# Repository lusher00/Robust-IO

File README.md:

# Robust IO

A rugged industrial I/O board designed in KiCad 10.

## Status

- **Rev A:** fabricated and assembled by JLCPCB (5 bare boards, 2 assembled),
  ordered 2026-10-05. Board 1 passes bring-up: power rails, MCU, UART
  console, MC33978 inputs (after replacing U7), MCP2515 CAN at 250 kbit/s
  with a BeagleBone Blue host, and all 8 outputs under TUI and CAN control
  (OUT_0's indicator LED is dead; the output itself works). Load test:
  OUT_0 to OUT_3 on together at about 3.7 A each, 14.8 A from 24 V, board
  cool on IR. Board 2 is partly disassembled from
  the reverse-polarity incident and needs C44/C45, U5, U1, U14 and one
  BTS7008 refitted.
- **Rev B:** change list collected below. The KiCad project in
  `hardware/rev-b/` starts as a copy of rev A.
- **Schematic:** complete across four hierarchical sheets. ERC clean.
- **PCB layout:** fully routed. DRC reports 0 errors and 4 library-mismatch
  warnings (J20, U1, U14, U7), which are intentional local footprint edits.

## Board

| Item | Value |
|---|---|
| Size | 160 x 100 mm, four M3 mounting holes |
| Layers | 4: F.Cu signal, In1 GND plane, In2 +24V plane, B.Cu signal |
| Copper | 2 oz outer, 1 oz inner |
| Minimum drill | 0.3 mm |
| Supply | 24 V nominal through a blade fuse (F1) and SMDJ24A TVS |
| Assembly | SMD parts on top side only; through-hole connectors and fuse holder hand-fitted |

## Architecture

| Sheet | Contents |
|---|---|
| `power` | Two TPS560430 buck regulators (+5V, +3.3V), input fuse, TVS, bulk capacitors |
| `processor` | ATmega1284P, MCP2515 + MCP2562 (CAN), crystals, ISP header (J1), UART header (J20), reset button |
| `inputs` | MC33978 22-channel switch detect with fused, filtered inputs and status LEDs |
| `outputs2` | Four BTS7008-2EPA dual high-side switches (8 outputs), two DRV8876 motor drivers |

## Connectors

- **J1:** 2x3 2.54 mm SMD header, AVR ISP (SPI is also on test points).
- **J20:** 1x6 2.54 mm SMD header, 3.3 V TTL UART in FTDI cable pinout.
  RX and TX have series resistors and a TVS array.
- **J14, J19, J18, J16, J9, J10 (top edge):** 3.5 mm pluggable terminal
  headers for the switch inputs, each with a fused supply pin and ground.
- **J15 (bottom edge):** 24 V supply input and ground.
- **J3, J5 (bottom edge):** high-side outputs OUT_0 to OUT_7, with +24V and
  ground.
- **J6 (bottom edge):** two motor driver outputs, with +24V and ground.
- **J4 (left edge):** CAN bus, +5V and ground. SW1 is next to it.

## Test points

41 test points (35 top, 6 bottom) cover the supply rails, SPI, UART, CAN
interrupt, driver control and sense lines, and ground. Positions and nets are
listed in `hardware/rev-a/fab/robust-io-testpoints.csv`.

## Known limits of rev A

- **Supply polarity is not marked on the board.** J15 pins 1 and 2 (the
  square pad end, nearest F1) are +24V; pins 3 and 4 are GND. There is no
  reverse-polarity protection, so a reversed supply forward-biases D6 and the
  substrate diodes of every part on the rail. Both rev A boards were powered
  reversed during bring-up; see the Bring-up log.
- **MC33978 input LEDs read "input at ground".** Each input LED sits between
  +24V (2.2k) and the IC pin, so it lights when the input is pulled low.
  That is correct for switch-to-ground sensing, which is all rev A
  supports; switch-to-battery on an SP channel needs that channel's LED
  removed, because the 2.2k sources more current than the IC can sink.
- **BTS7008 GND pins have no series resistor.** The datasheet calls for
  47 ohm in the GND pin (RGND) and limits GND pin current to 50 mA.
- **CS_CAN has no pull-up.** With the MCU in reset (during ISP) the MCP2515
  can drive MISO; programming is unreliable unless the board is power-cycled
  first. Fit 10k from TP8 to TP1 if it keeps failing.
- **UART activity LEDs load the lines.** C69/C70 (10 nF) with the 1k series
  resistors give a 10 us edge, too slow for 115200 baud. The console runs at
  38400 on rev A.
- **C57 to C60 use a polarized symbol** in the schematic; the fitted parts
  are 50 V MLCCs and have no polarity.

- The BTS7008-2EPA is rated for a 28 V maximum supply. Use a regulated 24 V
  supply; do not connect directly to a charging battery system.
- Reverse polarity protection is the fuse and TVS only. There is no series
  reverse-blocking stage.
- The input polyfuses are rated 30 V, which is a small margin over 24 V.
- Y1 load capacitors (22 pF) have not been matched to the crystal's
  specified load capacitance.
- Regulator output tracks are 0.2 mm wide.

## Bring-up log (rev A)

- Both boards were first powered with the supply reversed. The symptom was a
  rail that read like a diode (0.5 V both ways, about 2 Ohm at 1 A), with
  whichever part had the lowest forward drop getting warm: D6, then U5,
  then the BTS7008 switches and DRV8876 drivers as parts were removed. With
  the supply in current limit at about 1 V nothing was damaged except C44
  and C45 on board 2, which vented after conducting in reverse for a long
  time. D6 was correctly placed on both boards; the earlier CPL change for
  it has been reverted.
- Board 1 after correct power: 5 V and 3.3 V present, fuses written
  (JTAG off), firmware flashed from a Raspberry Pi over J1, console at
  38400 8N1 on J20, MCP2515 answers. MC33978 does not answer the SPI check:
  continuity from the MCU to U7 pins 2, 3, 4, 16, 31 and 32 is good, VBATP
  and VDDQ are present, all four SPI modes were tried. The MISO pull-up
  test in firmware 0.3 (`MC33978 check frames` line in the banner) is the
  next step: 0xFFFFFFFF means the chip never drives MISO, 0x00000000 means
  it is selected but not shifting.
- With JTAG enabled (fresh chip) outputs 2 to 5 switch on by themselves.
  They go off once the fuses are written.
- On a Pi 4, avrdude leaves GPIO25 (reset) driven low after it exits. Run
  `pinctrl set 25 ip pu` (or `raspi-gpio set 25 ip pu`) after programming,
  or unplug J1 pin 5, before expecting the board to run.
- The Pi's mini UART (`/dev/ttyS0`) is unreliable for the console even at
  38400. Use an FTDI cable on J20 for the console and the Pi only for
  programming, or switch the Pi to the PL011 (`dtoverlay=disable-bt`).

## Rev B change list

- MCU: replace the ATmega1284P + MCP2515 with an STM32G474 (Cortex-M4,
  170 MHz, 3 native FDCAN, 5 ADCs, HRTIM/advanced timers, native USB).
  Board CAN becomes CAN FD with an FD-rated transceiver. Programming over
  SWD (Tag-Connect or 10-pin header; Blue via OpenOCD, or the ESP32 over
  Wi-Fi). Freed pins mean the ESP32-S3 links to the MCU over a UART
  instead of joining the CAN bus (its TWAI is classic only and would break
  an FD bus), and USB-CAN runs on the G474's own USB. Firmware: drivers and
  CAN protocol port in C; the HAL layer is rewritten. An M7 (STM32H723)
  only if robust-io needs Ethernet itself.
- Mark + and - on the silkscreen at J15.
- 24 V input protection front end, in order from J15: F1 blade fuse, a
  surge stopper / ideal-diode controller rated for at least 100 V
  (LTC4368/LT4363 class) with back-to-back 100 V N-FETs, then the rail TVS
  after the FETs. The controller gives reverse polarity (to -40 V or
  better), overvoltage cutoff at about 30 V set by divider, undervoltage
  lockout, a forward/reverse overcurrent circuit breaker and soft-start for
  hot-plug inrush. Any TVS ahead of the FETs is bidirectional with a
  standoff above the worst wrong supply (SMDJ64CA class), so reverse
  polarity or a 48 to 60 V supply turns the board off instead of clamping
  and blowing F1. A rev A board was hit with 60 V on 2026-11-07: the
  SMDJ24A clamped, both 10 A fuses blew and the rail was left shorted.
  Move the bulk capacitors after the controller and rate them 100 V. Add a
  supply monitor (INA228-class: bus voltage, total current, fault alert) on
  the MCU so input V/I and protection trips are reported over CAN.
- Input indicator LEDs: two-lead bicolour LED (red/green) in series with each
  input, replacing the 2.2k pull-ups R62 to R83, so the LED shows current in
  either direction and switch-to-battery works on the SP channels. Checked
  against the MC33978 datasheet: detection threshold 4.0 V (3.7 to 4.3 V,
  80 to 300 mV hysteresis), sustain 2.0 mA SG / 2.2 mA SB. SG closed sits at
  the LED drop (about 2 V), at least 1.4 V under the minimum threshold; SB
  closed sits near +24V minus the drop. Use high-efficiency LEDs, visible at
  2 mA and rated for the 20 mA maximum wetting pulse. Do not use low-power
  mode (SG threshold 100 to 300 mV, below the LED drop) or the 2.5 V
  threshold option on these inputs. Put the LED after the input filter and
  clamp so field transients do not pass through it.
- 47 ohm in series with each BTS7008 GND pin (U8 to U11).
- C69/C70 to 220 pF, or drive the UART LEDs from the MCU.
- C57 to C60: non-polarized capacitor symbol.
- Test points: Keystone 5015 SMT loops on the rails, SPI, UART, interrupt,
  fault and analog sense lines; the four corner mounting holes are GND and
  take a ring lug, which covers the ground clips.
- SBC supply: 24 V to 5 V 5 A buck (Pi 5 / CM5) and 24 V to 12 V 3 A buck
  (BeagleBone Blue 9-18 V jack), each fused, on their own terminal block and
  fed from +24V ahead of the output switches so the host timeout cannot cut
  the host's own power.
- Use the bottom side: move the large SMC diodes (output clamps D2, D4,
  D8 to D13 B560C, D7 B340, input TVS D6) and other bulky parts to B.Cu for
  hand fitting, freeing top-side area around the output stage.
- Optional Wi-Fi/BLE: socket headers for a Waveshare ESP32-S3-Zero (same
  module as the POV project); the board works without it fitted. It joins
  the MCU over a UART (see MCU item), is wired to SWD and NRST/BOOT0 so it
  can reflash the MCU over Wi-Fi, and can bridge the console UART. Powered from +5V into the Zero's own regulator, so the +5V rail must
  cover its Wi-Fi peaks (about 350 to 500 mA).
  Bridge functions on the S3 (classic CAN only; CAN FD, Ethernet fieldbuses
  and Linux stay on the can-gateway):
  - Wi-Fi/BLE to CAN bridge: web UI, MQTT and a CAN socket for hosts.
  - USB-to-CAN adapter (candleLight/gs_usb class) on the G474's native USB
    via USB-C, so a Mac or PC gets a CAN FD interface.
  - One RS-485 port (Modbus RTU) from an S3 UART: transceiver, terminal
    block, switchable 120 ohm termination and bias.
- 16 high-side outputs, all on the protected 9 to 28 V input (12 V and
  24 V systems; vehicle load dump handled by the input front end):
  - OUT_0 to OUT_7: keep the four BTS7008-2EPA (7.5 A per channel).
  - OUT_8 to OUT_15: four 24 V-family duals (BTT6030-2ERA or TPS272C45,
    pick at schematic time), with margin above 28 V.
  - Each bank has its own output-power terminal, fed from the main input by
    default, so an E-stop or safety relay can cut output power while the MCU
    stays up and reporting. No separate 36 V injection.
  Size connector GND/supply pins per bank (rev A has one GND pin per four
  outputs on J3/J5).
- Replace the two DRV8876 (current limit fixed at about 1.36 A by
  resistors, too low for typical 2 to 5 A linear actuators) with two quad
  half-bridges (8 half-bridges), DRV8962 class (about 65 V, 5 A per half-bridge; confirm in
  the datasheet). Current limit set from a G474 DAC instead of fixed
  resistors, with per-half-bridge current sense to the ADC. Each
  half-bridge is configured in firmware as a high-side or low-side output,
  or paired for reversing: up to four reversing motors or linear actuators,
  four latching irrigation valve zones, two bipolar steppers, or any mix.
  Needs about 16 MCU control pins plus sense and fault lines (G474 in
  LQFP100).
- 4 relay outputs, dry contact (SPDT), for AC loads: 24 VAC irrigation
  valves, pump/fan contactor coils. Mains loads go through external
  contactors.
- Analog inputs: 4 channels, each jumper or software selectable 4-20 mA /
  0-10 V, protected, on G474 ADCs (tank level, pressure, soil moisture).
- 2 fast pulse inputs on G474 timer pins for flow meters and encoders.
- LoRa (SX1262 module) on the ESP32 side for remote sites beyond Wi-Fi.
- Connectors: replace Phoenix MSTBA/MC with LCSC-stocked equivalents of the
  same pitch (Degson/Kefa/Dinkle 5.08 mm for power, outputs and motors,
  3.5 mm for inputs; plugs about $0.30 to $1 instead of about $7), and
  standardize on as few pin counts as possible so one plug type covers
  each group. Prefer push-in spring plugs for the inputs.

## Repository layout

| Folder | Content |
|---|---|
| `hardware/rev-a/` | Rev A as built (git tag `rev-a`): KiCad project, `fab/` outputs and parts orders, `docs/` drawings and photos, `fixture/` bench fixture |
| `hardware/rev-b/` | Rev B KiCad project, in progress |
| `firmware/` | ATmega1284P firmware for rev A |
| `tools/` | Host tools, shared by both revisions (same CAN protocol) |
| `manufacturers datasheets/` | Part datasheets |

Rev A files stay as they were built; all new hardware work happens in
`hardware/rev-b/`.

### Rev A KiCad files (`hardware/rev-a/`)

- `robust-io.kicad_pro` - project file
- `robust-io.kicad_sch` - root sheet
- `power.kicad_sch`, `processor.kicad_sch`, `inputs.kicad_sch`, `outputs2.kicad_sch` - schematic sheets
- `robust-io.kicad_pcb` - PCB layout
- `robust-io.kicad_sym`, `sym-lib-table` - project symbol library
- `robust-io.kicad_dru` - custom design rules
- `DRC.rpt`, `ERC.rpt` - latest check reports

## Documentation (`hardware/rev-a/docs/`)

| File | Content |
|---|---|
| [robust-io-schematic.pdf](hardware/rev-a/docs/robust-io-schematic.pdf) | Schematic, all sheets |
| [layout-top.pdf](hardware/rev-a/docs/layout-top.pdf), [layout-bottom.pdf](hardware/rev-a/docs/layout-bottom.pdf) | Copper and silkscreen per side |
| [assembly-top.pdf](hardware/rev-a/docs/assembly-top.pdf) | Assembly drawing with reference designators |
| [board-top.png](hardware/rev-a/docs/board-top.png), [board-bottom.png](hardware/rev-a/docs/board-bottom.png), [board-angle.png](hardware/rev-a/docs/board-angle.png) | 3D renders |
| [robust-io-revA-top.jpg](hardware/rev-a/docs/robust-io-revA-top.jpg), [robust-io-revA-top-board-only.jpg](hardware/rev-a/docs/robust-io-revA-top-board-only.jpg) | Photos of the assembled rev A board (composite of several exposures, rectified to the board outline) |

Regenerate with `bash hardware/rev-a/docs/make_docs.sh` after saving the schematic and board.

## Firmware (`firmware/`)

ATmega1284P firmware 0.3: UART service console (38400 8N1), CAN protocol with
host timeout, output current trip, motor control, EEPROM settings and a
self-test. Runs on rev A hardware; the MC33978 driver is unverified until the
chip answers (see Bring-up log). Build with `make` in `firmware/` (avr-gcc); `make fuses` and
`make flash` program the board from a Raspberry Pi wired to J1. See
[firmware/DESIGN.md](firmware/DESIGN.md) for the pin map, console commands,
CAN frame layouts and settings.

## Host tools (`tools/`)

Everything for talking to the board over CAN from a Pi, laptop or robot:
a DBC file, a Python package with the `robustio` command-line tool, a terminal
dashboard, a browser dashboard, a bring-up and end-of-line test runner that
writes a report per board, a ROS 2 driver node, and `canweb`, a CAN
diagnostic web app for a Pi with a transceiver (live bus view, DBC decode,
send, log, and a Robust IO page with input lights, output buttons and current
graphs; other products plug in as a Python class). All of them also run
against the firmware simulator, so they can be used before hardware exists.
See [tools/README.md](tools/README.md).

## Fabrication outputs (`hardware/rev-a/fab/`)

| File | Purpose |
|---|---|
| `make_gerbers.sh` | Plots Gerbers, drill files and the position file with kicad-cli, then zips the Gerbers |
| `gerbers/`, `robust-io-gerbers.zip` | Gerber and Excellon drill files |
| `robust-io-BOM-JLC-smd.csv` | JLCPCB assembly BOM, 50 lines, LCSC part number on every line |
| `robust-io-CPL-JLC.csv` | JLCPCB placement file |
| `cpl_rotation_offsets.json` | Per-part rotation corrections applied to the placement file |
| `kicad-pos.csv` | Raw KiCad position export |
| `robust-io-BOM-tht.csv` | Through-hole parts to fit by hand (fuse holder, terminal headers) |
| `robust-io-testpoints.csv` | Test point list with nets and positions |
| `robust-io-fab-all.zip` | Everything above in one archive |

To regenerate the Gerbers after a board change, save the board in KiCad and run:

    bash hardware/rev-a/fab/make_gerbers.sh

The placement file is not produced by the script. JLCPCB's rotation
convention differs from KiCad's for some packages, so the rotation for each
part in `robust-io-CPL-JLC.csv` is the KiCad rotation plus the offset in
`cpl_rotation_offsets.json`. Regenerate it whenever parts move, and check
the result in JLCPCB's placement preview before ordering.

## Bring-up order

1. Fit F1 and J15. Apply 24 V from a current-limited supply with nothing else
   connected.
2. Check +5V (TP2) and +3.3V (TP1) against ground.
3. Wire the Raspberry Pi to J1 (`firmware/DESIGN.md` section 4) and run
   `make fuses`, then `make flash`, in `firmware/`. Do this before connecting
   any load to J3 or J5: until the fuses disable JTAG, outputs 2 to 5 can
   switch on by themselves. Release the reset line afterward
   (`pinctrl set 25 ip pu`).
4. On the J20 console (FTDI cable, 38400 8N1): `ver`, then `selftest`.
5. Connect CAN and run `robustio bringup --console /dev/serial0 --serial <n>`
   from `tools/`, which writes a report for the board.
6. Connect loads and enable the outputs and motor drivers one channel at a time
   (`robustio bringup --loads` once all are connected).

## License

See [LICENSE](LICENSE). Free for personal, educational, and open-source use.
For commercial licensing, contact ryan.lush@gmail.com.

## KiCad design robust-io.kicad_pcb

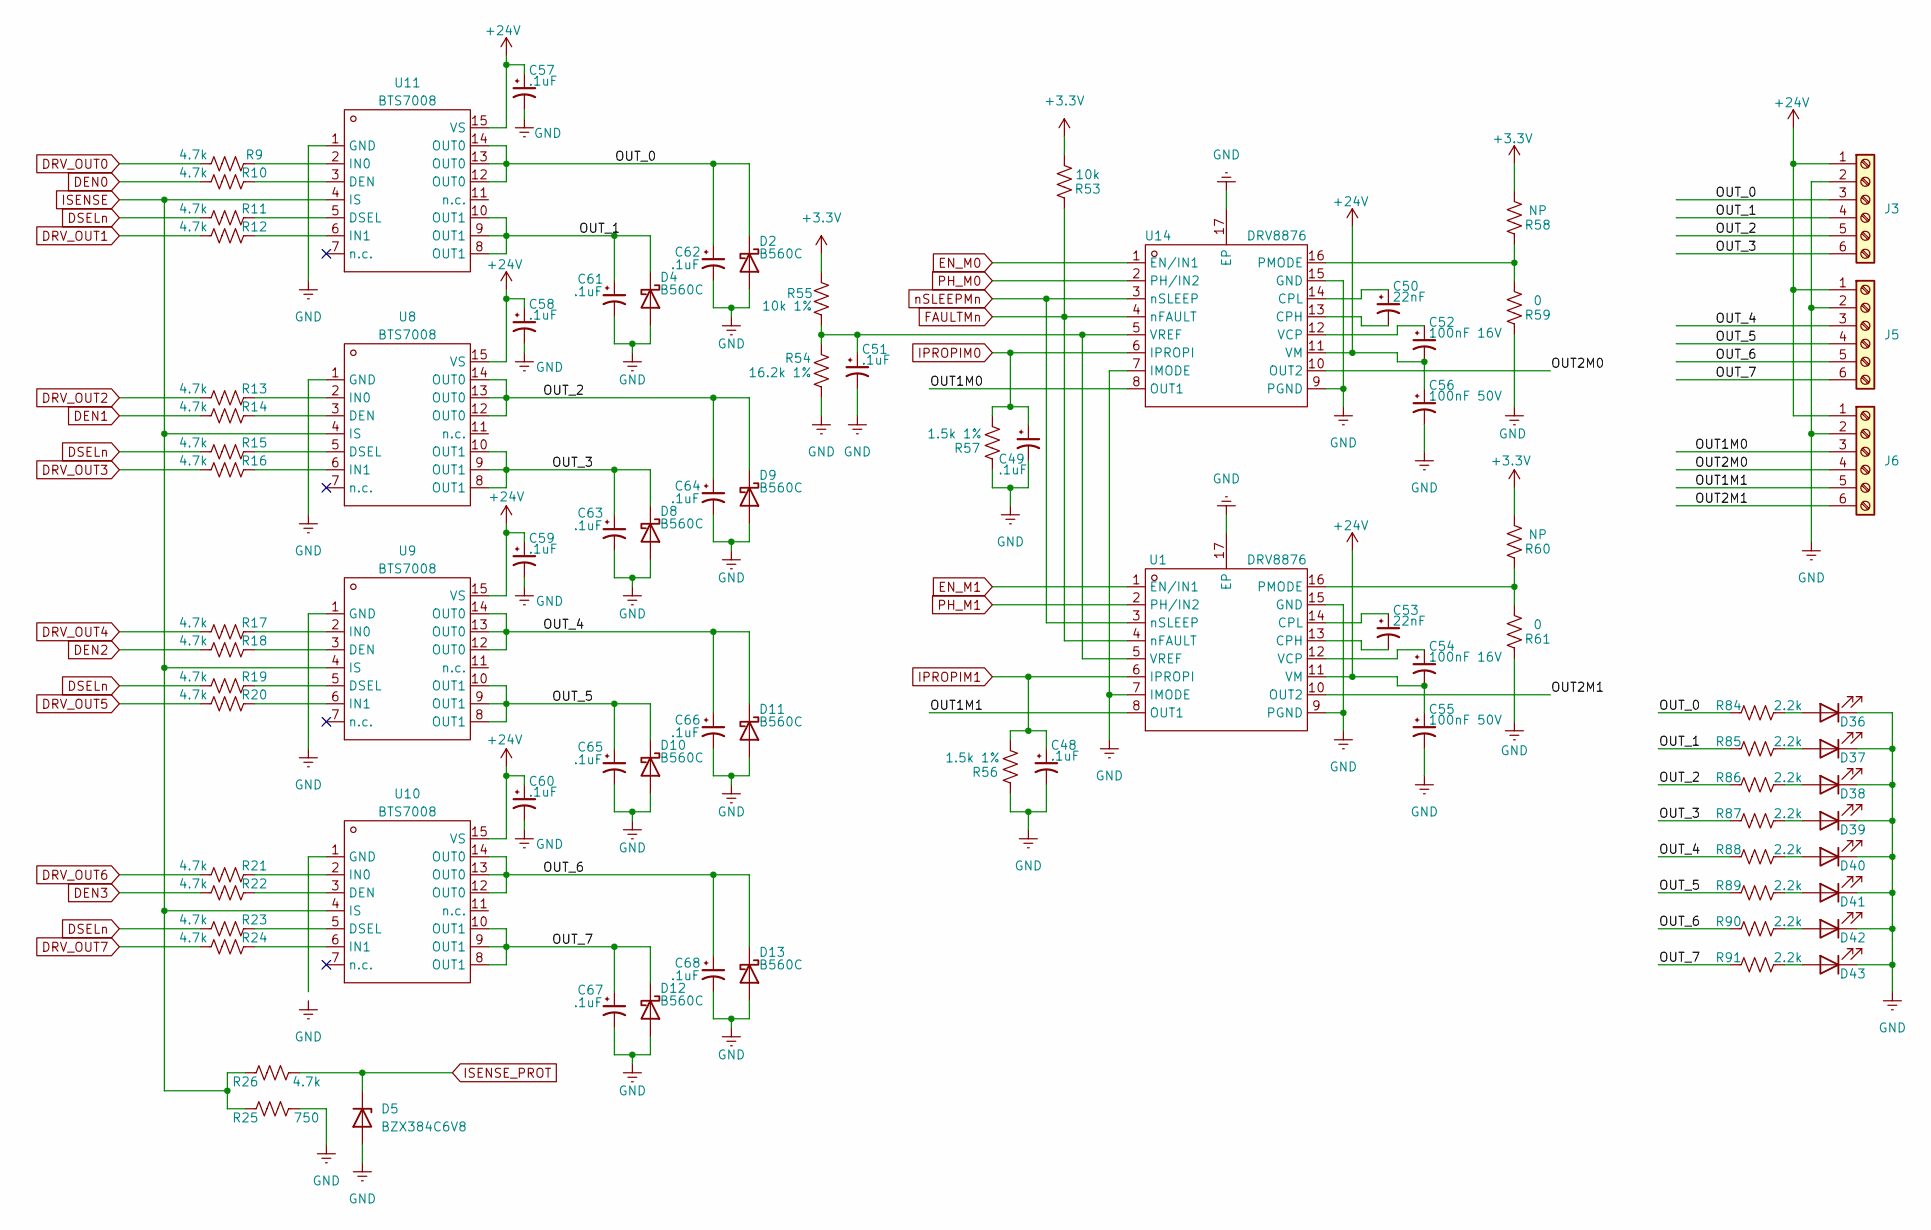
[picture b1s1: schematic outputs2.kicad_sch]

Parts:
C48, C49, C51, C57, C58, C59, C60, C61, C62, C63, C64, C65, C66, C67, C68: .1uF; C_0603_1608Metric_Pad1.08x0.95mm_HandSolder
C50, C53: 22nF; C_0603_1608Metric_Pad1.08x0.95mm_HandSolder
C52, C54: 100nF 16V; C_0603_1608Metric_Pad1.08x0.95mm_HandSolder
C55, C56: 100nF 50V; C_0603_1608Metric_Pad1.08x0.95mm_HandSolder
D2, D4, D8, D9, D10, D11, D12, D13: B560C; D_SMC
D5: BZX384C6V8; D_SOD-323
D36, D37, D38, D39, D40, D41, D42, D43: LED; LED_0603_1608Metric
J3, J5, J6: Screw_Terminal_01x06; PhoenixContact_MSTBA_2,5_6-G-5,08_1x06_P5.08mm_Horizontal
R9, R10, R11, R12, R13, R14, R15, R16, R17, R18, R19, R20, R21, R22, R23, R24, R26: 4.7k; R_0603_1608Metric
R25: 750; R_0603_1608Metric
R53: 10k; R_0603_1608Metric_Pad0.98x0.95mm_HandSolder
R54: 16.2k 1%; R_0603_1608Metric_Pad0.98x0.95mm_HandSolder
R55: 10k 1%; R_0603_1608Metric_Pad0.98x0.95mm_HandSolder
R56, R57: 1.5k 1%; R_0603_1608Metric_Pad0.98x0.95mm_HandSolder
R58, R60: NP; R_0603_1608Metric_Pad0.98x0.95mm_HandSolder
R59, R61: 0; R_0603_1608Metric_Pad0.98x0.95mm_HandSolder
R84, R85, R86, R87, R88, R89, R90, R91: 2.2k; R_0603_1608Metric_Pad0.98x0.95mm_HandSolder
U1, U14: DRV8876; IC_DRV8876PWPR; Manufacturer Part DRV8876PWPR; LCSC Part Name 3.5A 有刷直流电机驱动芯片 5.5V
U8, U9, U10, U11: BTS7008; TSSOP-14-1EP_4.4x5mm_P0.65mm; Manufacturer Part BTS7008-2EPA; LCSC Part Name 12V智能高端功率开关

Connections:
+3.3V: R53.1, R55.1, R58.1, R60.1; also elsewhere on the board
+24V: C52.2, C54.2, C55.1, C56.1, C57.1, C58.1, C59.1, C60.1, J3.1, J5.1, J6.1, U1.11 (VM), U8.15 (VS), U9.15 (VS), U10.15 (VS), U11.15 (VS), U14.11 (VM); also elsewhere on the board
/outputs2/OUT1M0: J6.3, U14.8 (OUT1)
/outputs2/OUT1M1: J6.5, U1.8 (OUT1)
/outputs2/OUT2M0: J6.4, U14.10 (OUT2)
/outputs2/OUT2M1: J6.6, U1.10 (OUT2)
/outputs2/OUT_0: C62.1, D2.1 (K), J3.3, R84.1, U11.12 (OUT0), U11.13 (OUT0), U11.14 (OUT0)
/outputs2/OUT_1: C61.1, D4.1 (K), J3.4, R85.1, U11.8 (OUT1), U11.9 (OUT1), U11.10 (OUT1)
/outputs2/OUT_2: C64.1, D9.1 (K), J3.5, R86.1, U8.12 (OUT0), U8.13 (OUT0), U8.14 (OUT0)
/outputs2/OUT_3: C63.1, D8.1 (K), J3.6, R87.1, U8.8 (OUT1), U8.9 (OUT1), U8.10 (OUT1)
/outputs2/OUT_4: C66.1, D11.1 (K), J5.3, R88.1, U9.12 (OUT0), U9.13 (OUT0), U9.14 (OUT0)
/outputs2/OUT_5: C65.1, D10.1 (K), J5.4, R89.1, U9.8 (OUT1), U9.9 (OUT1), U9.10 (OUT1)
/outputs2/OUT_6: C68.1, D13.1 (K), J5.5, R90.1, U10.12 (OUT0), U10.13 (OUT0), U10.14 (OUT0)
/outputs2/OUT_7: C67.1, D12.1 (K), J5.6, R91.1, U10.8 (OUT1), U10.9 (OUT1), U10.10 (OUT1)
DEN0: R10.1; also elsewhere on the board
DEN1: R14.1; also elsewhere on the board
DEN2: R18.1; also elsewhere on the board
DEN3: R22.1; also elsewhere on the board
DRV_OUT0: R9.1; also elsewhere on the board
DRV_OUT1: R12.1; also elsewhere on the board
DRV_OUT2: R13.1; also elsewhere on the board
DRV_OUT3: R16.1; also elsewhere on the board
DRV_OUT4: R17.1; also elsewhere on the board
DRV_OUT5: R20.1; also elsewhere on the board
DRV_OUT6: R21.1; also elsewhere on the board
DRV_OUT7: R24.1; also elsewhere on the board
DSELn: R11.1, R15.1, R19.1, R23.1; also elsewhere on the board
EN_M0: U14.1 (EN/IN1); also elsewhere on the board
EN_M1: U1.1 (EN/IN1); also elsewhere on the board
FAULTMn: R53.2, U1.4 (nFAULT), U14.4 (nFAULT); also elsewhere on the board
GND: C48.2, C49.2, C51.2, C55.2, C56.2, C57.2, C58.2, C59.2, C60.2, C61.2, C62.2, C63.2, C64.2, C65.2, C66.2, C67.2, C68.2, D2.2 (A), D4.2 (A), D5.2 (A), D8.2 (A), D9.2 (A), D10.2 (A), D11.2 (A), D12.2 (A), D13.2 (A), D36.1 (K), D37.1 (K), D38.1 (K), D39.1 (K), D40.1 (K), D41.1 (K), D42.1 (K), D43.1 (K), J3.2, J5.2, J6.2, R25.1, R54.2, R56.2, R57.2, R59.2, R61.2, U1.7 (IMODE), U1.9 (PGND), U1.15 (GND), U1.17 (EP), U8.1 (GND), U9.1 (GND), U11.1 (GND), U14.7 (IMODE), U14.9 (PGND), U14.15 (GND), U14.17 (EP); also elsewhere on the board
IPROPIM0: C49.1, R57.1, U14.6 (IPROPI); also elsewhere on the board
IPROPIM1: C48.1, R56.1, U1.6 (IPROPI); also elsewhere on the board
ISENSE: R25.2, R26.2, U8.4 (IS), U9.4 (IS), U10.4 (IS), U11.4 (IS)
ISENSE_PROT: D5.1 (K), R26.1; also elsewhere on the board
unnamed: D36.2 (A), R84.2
unnamed: D37.2 (A), R85.2
unnamed: D38.2 (A), R86.2
unnamed: D39.2 (A), R87.2
unnamed: D40.2 (A), R88.2
unnamed: D41.2 (A), R89.2
unnamed: D42.2 (A), R90.2
unnamed: D43.2 (A), R91.2
unnamed: C53.2, U1.13 (CPH)
unnamed: C53.1, U1.14 (CPL)
unnamed: R60.2, R61.1, U1.16 (PMODE)
unnamed: C54.1, U1.12 (VCP)
unnamed: C51.1, R54.1, R55.2, U1.5 (VREF), U14.5 (VREF)
unnamed: R14.2, U8.3 (DEN)
unnamed: R15.2, U8.5 (DSEL)
unnamed: R13.2, U8.2 (IN0)
unnamed: R16.2, U8.6 (IN1)
unnamed: R18.2, U9.3 (DEN)
unnamed: R19.2, U9.5 (DSEL)
unnamed: R17.2, U9.2 (IN0)
unnamed: R20.2, U9.6 (IN1)
unnamed: R22.2, U10.3 (DEN)
unnamed: R23.2, U10.5 (DSEL)
unnamed: R21.2, U10.2 (IN0)
unnamed: R24.2, U10.6 (IN1)
unnamed: R10.2, U11.3 (DEN)
unnamed: R11.2, U11.5 (DSEL)
unnamed: R9.2, U11.2 (IN0)
unnamed: R12.2, U11.6 (IN1)
unnamed: C50.2, U14.13 (CPH)
unnamed: C50.1, U14.14 (CPL)
unnamed: R58.2, R59.1, U14.16 (PMODE)
unnamed: C52.1, U14.12 (VCP)
PH_M0: U14.2 (PH/IN2); also elsewhere on the board
PH_M1: U1.2 (PH/IN2); also elsewhere on the board
nSLEEPMn: U1.3 (nSLEEP), U14.3 (nSLEEP); also elsewhere on the board

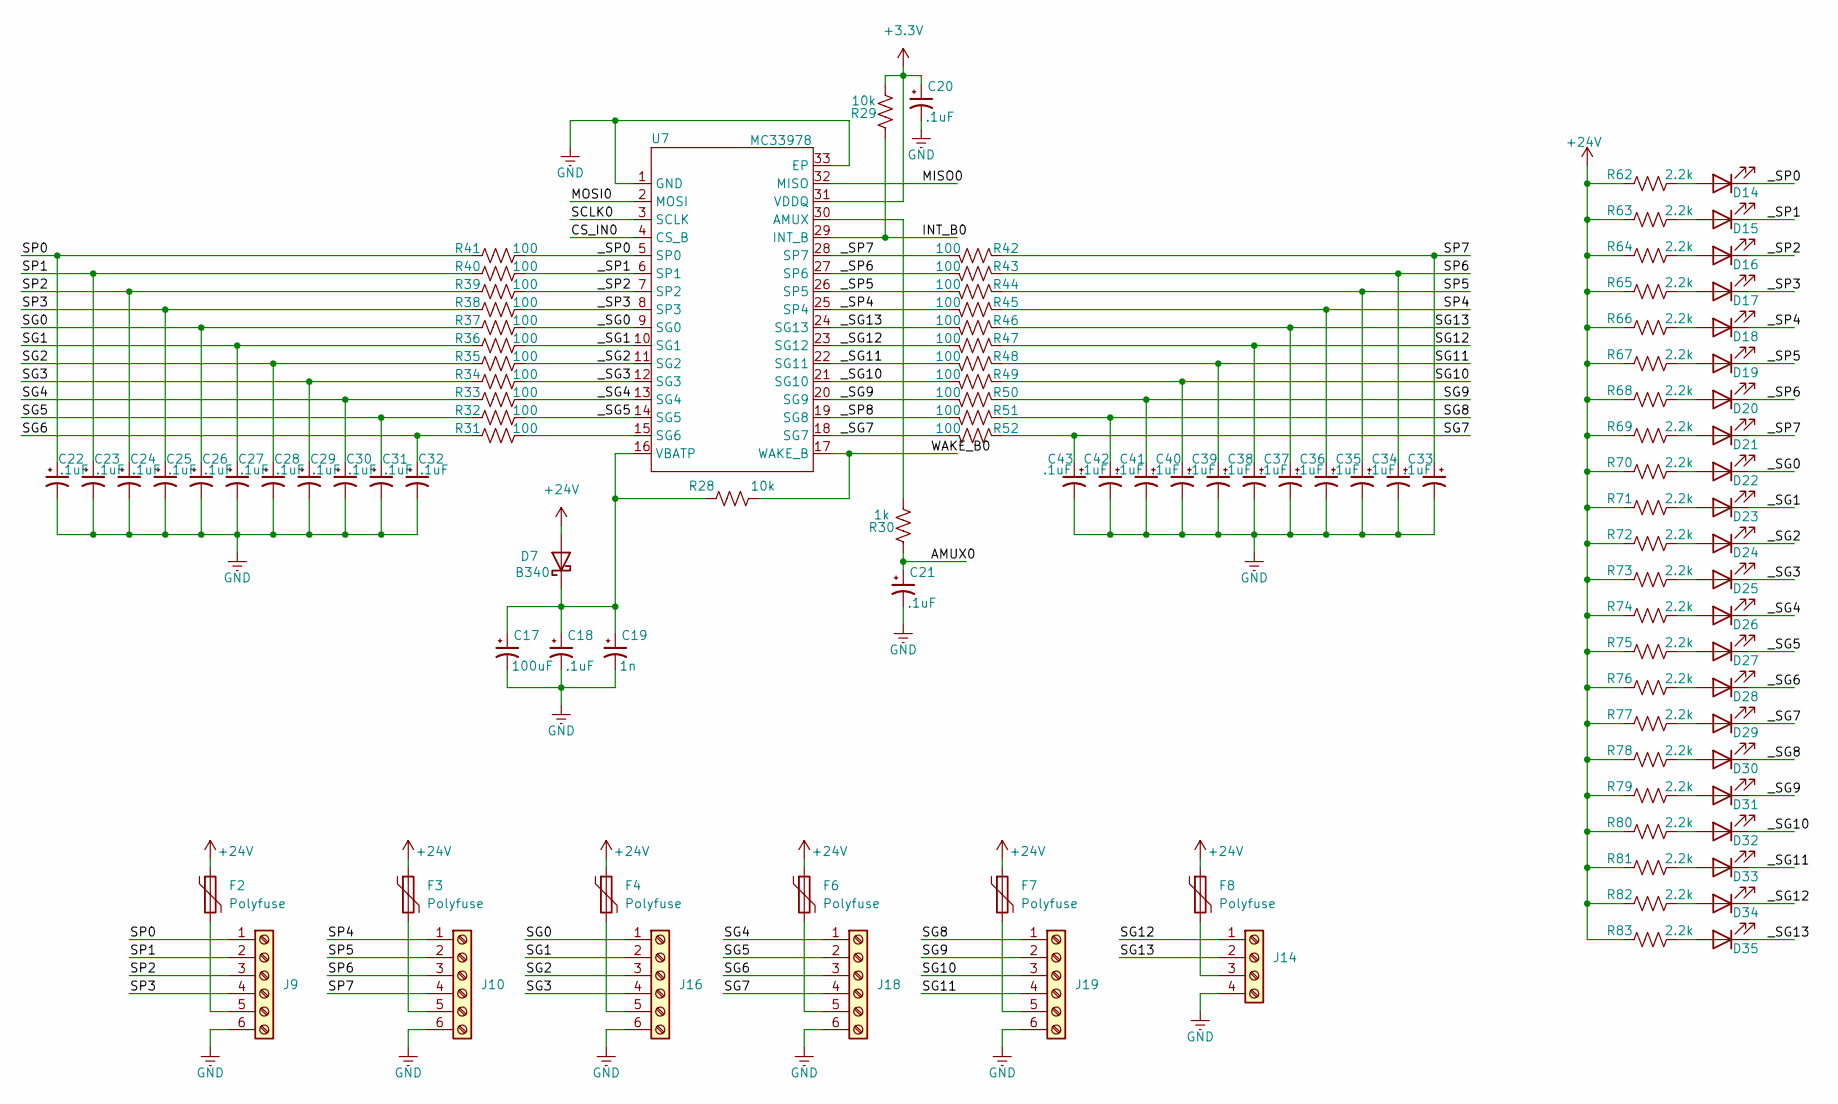
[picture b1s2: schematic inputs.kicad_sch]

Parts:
C17: 100uF; C_0603_1608Metric
C18, C20, C21, C22, C23, C24, C25, C26, C27, C28, C29, C30, C31, C32, C33, C34, C35, C36, C37, C38, C39, C40, C41, C42, C43: .1uF; C_0603_1608Metric
C19: 1n; C_0603_1608Metric
D7: B340; D_SMC
D14, D15, D16, D17, D18, D19, D20, D21, D22, D23, D24, D25, D26, D27, D28, D29, D30, D31, D32, D33, D34, D35: LED; LED_0603_1608Metric
F2, F3, F4, F6, F7, F8: Polyfuse; Fuse_1206_3216Metric
J9, J10, J16, J18, J19: Screw_Terminal_01x06; PhoenixContact_MC_1,5_6-G-3.5_1x06_P3.50mm_Horizontal
J14: Screw_Terminal_01x04; PhoenixContact_MC_1,5_4-G-3.5_1x04_P3.50mm_Horizontal
R28, R29: 10k; R_0603_1608Metric_Pad0.98x0.95mm_HandSolder
R30: 1k; R_0603_1608Metric_Pad0.98x0.95mm_HandSolder
R31, R32, R33, R34, R35, R36, R37, R38, R39, R40, R41, R42, R43, R44, R45, R46, R47, R48, R49, R50, R51, R52: 100; R_0603_1608Metric_Pad0.98x0.95mm_HandSolder
R62, R63, R64, R65, R66, R67, R68, R69, R70, R71, R72, R73, R74, R75, R76, R77, R78, R79, R80, R81, R82, R83: 2.2k; R_1206_3216Metric
U7: MC33978; QFN-32-1EP_5x5mm_P0.5mm_EP3.7x3.7mm_ThermalVias; Manufacturer Part MC33978AEKR2; LCSC Part Name MC33978AEKR2

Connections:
+3.3V: C20.1, R29.2, U7.31 (VDDQ); also elsewhere on the board
+24V: D7.2 (A), F2.1, F3.1, F4.1, F6.1, F7.1, F8.1, R62.1, R63.1, R64.1, R65.1, R66.1, R67.1, R68.1, R69.1, R70.1, R71.1, R72.1, R73.1, R74.1, R75.1, R76.1, R77.1, R78.1, R79.1, R80.1, R81.1, R82.1, R83.1; also elsewhere on the board
/inputs/SG0: C26.1, J16.1, R37.1
/inputs/SG1: C27.1, J16.2, R36.1
/inputs/SG2: C28.1, J16.3, R35.1
/inputs/SG3: C29.1, J16.4, R34.1
/inputs/SG4: C30.1, J18.1, R33.1
/inputs/SG5: C31.1, J18.2, R32.1
/inputs/SG6: C32.1, J18.3, R31.1
/inputs/SG7: C43.1, J18.4, R52.1
/inputs/SG8: C42.1, J19.1, R51.1
/inputs/SG9: C41.1, J19.2, R50.1
/inputs/SG10: C40.1, J19.3, R49.1
/inputs/SG11: C39.1, J19.4, R48.1
/inputs/SG12: C38.1, J14.1, R47.1
/inputs/SG13: C37.1, J14.2, R46.1
/inputs/SP0: C22.1, J9.1, R41.1
/inputs/SP1: C23.1, J9.2, R40.1
/inputs/SP2: C24.1, J9.3, R39.1
/inputs/SP3: C25.1, J9.4, R38.1
/inputs/SP4: C36.1, J10.1, R45.1
/inputs/SP5: C35.1, J10.2, R44.1
/inputs/SP6: C34.1, J10.3, R43.1
/inputs/SP7: C33.1, J10.4, R42.1
/inputs/_SG0: D22.1 (K), R37.2, U7.9 (SG0)
/inputs/_SG1: D23.1 (K), R36.2, U7.10 (SG1)
/inputs/_SG2: D24.1 (K), R35.2, U7.11 (SG2)
/inputs/_SG3: D25.1 (K), R34.2, U7.12 (SG3)
/inputs/_SG4: D26.1 (K), R33.2, U7.13 (SG4)
/inputs/_SG5: D27.1 (K), R32.2, U7.14 (SG5)
/inputs/_SG7: D29.1 (K), R52.2, U7.18 (SG7)
/inputs/_SG9: D31.1 (K), R50.2, U7.20 (SG9)
/inputs/_SG10: D32.1 (K), R49.2, U7.21 (SG10)
/inputs/_SG11: D33.1 (K), R48.2, U7.22 (SG11)
/inputs/_SG12: D34.1 (K), R47.2, U7.23 (SG12)
/inputs/_SG13: D35.1 (K), R46.2, U7.24 (SG13)
/inputs/_SP0: D14.1 (K), R41.2, U7.5 (SP0)
/inputs/_SP1: D15.1 (K), R40.2, U7.6 (SP1)
/inputs/_SP2: D16.1 (K), R39.2, U7.7 (SP2)
/inputs/_SP3: D17.1 (K), R38.2, U7.8 (SP3)
/inputs/_SP4: D18.1 (K), R45.2, U7.25 (SP4)
/inputs/_SP5: D19.1 (K), R44.2, U7.26 (SP5)
/inputs/_SP6: D20.1 (K), R43.2, U7.27 (SP6)
/inputs/_SP7: D21.1 (K), R42.2, U7.28 (SP7)
AMUX0: C21.1, R30.1; also elsewhere on the board
CS_IN0: U7.4 (CS_B); also elsewhere on the board
GND: C17.2, C18.2, C19.2, C20.2, C21.2, C22.2, C23.2, C24.2, C25.2, C26.2, C27.2, C28.2, C29.2, C30.2, C31.2, C32.2, C33.2, C34.2, C35.2, C36.2, C37.2, C38.2, C39.2, C40.2, C41.2, C42.2, C43.2, J9.6, J10.6, J14.4, J16.6, J18.6, J19.6, U7.1 (GND), U7.33 (EP); also elsewhere on the board
INT_B0: R29.1, U7.29 (INT_B); also elsewhere on the board
MISO0: U7.32 (MISO); also elsewhere on the board
MOSI0: U7.2 (MOSI); also elsewhere on the board
unnamed: C17.1, C18.1, C19.1, D7.1 (K), R28.1, U7.16 (VBATP)
unnamed: D14.2 (A), R62.2
unnamed: D15.2 (A), R63.2
unnamed: D16.2 (A), R64.2
unnamed: D17.2 (A), R65.2
unnamed: D18.2 (A), R66.2
unnamed: D19.2 (A), R67.2
unnamed: D20.2 (A), R68.2
unnamed: D21.2 (A), R69.2
unnamed: D22.2 (A), R70.2
unnamed: D23.2 (A), R71.2
unnamed: D24.2 (A), R72.2
unnamed: D25.2 (A), R73.2
unnamed: D26.2 (A), R74.2
unnamed: D27.2 (A), R75.2
unnamed: D28.2 (A), R76.2
unnamed: D29.2 (A), R77.2
unnamed: D30.2 (A), R78.2
unnamed: D31.2 (A), R79.2
unnamed: D32.2 (A), R80.2
unnamed: D33.2 (A), R81.2
unnamed: D34.2 (A), R82.2
unnamed: D35.2 (A), R83.2
unnamed: F2.2, J9.5
unnamed: F3.2, J10.5
unnamed: F8.2, J14.3
unnamed: F4.2, J16.5
unnamed: F6.2, J18.5
unnamed: F7.2, J19.5
unnamed: R30.2, U7.30 (AMUX)
unnamed: R28.2, U7.17 (WAKE_B)
SCLK0: U7.3 (SCLK); also elsewhere on the board

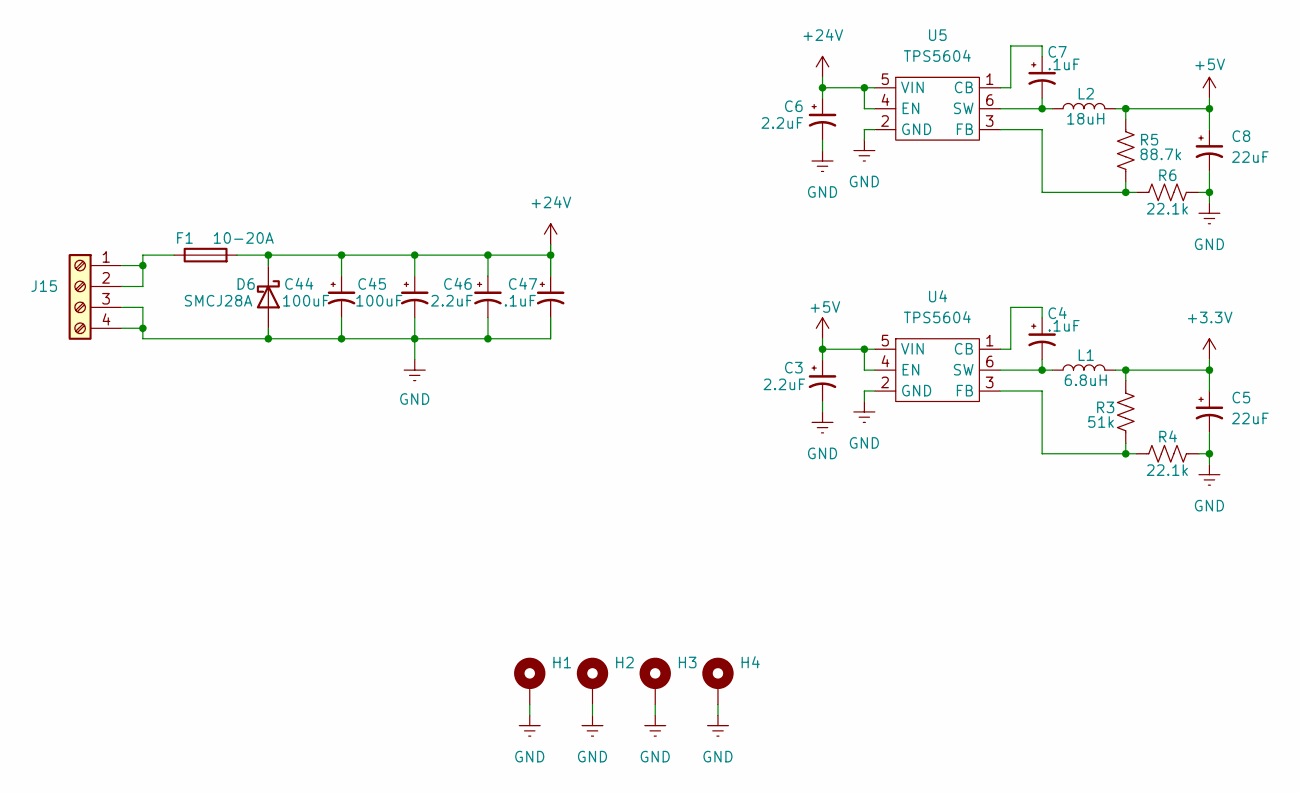
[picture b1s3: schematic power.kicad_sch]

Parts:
C3, C6, C46: 2.2uF; C_0805_2012Metric_Pad1.18x1.45mm_HandSolder
C4, C7: .1uF; C_0603_1608Metric_Pad1.08x0.95mm_HandSolder
C5, C8: 22uF; C_0603_1608Metric_Pad1.08x0.95mm_HandSolder
C44, C45: 100uF; C_0805_2012Metric_Pad1.18x1.45mm_HandSolder
C47: .1uF; C_0805_2012Metric_Pad1.18x1.45mm_HandSolder
D6: SMCJ28A; D_SMC
F1: 10-20A; Fuseholder_Blade_Mini_Keystone_3568
H1, H2, H3, H4: MountingHole_Pad; MountingHole_3.2mm_M3_DIN965_Pad_TopBottom
J15: Screw_Terminal_01x04; PhoenixContact_MSTBA_2,5_4-G-5,08_1x04_P5.08mm_Horizontal
L1: 6.8uH; L_0805_2012Metric_Pad1.05x1.20mm_HandSolder; Part Number CB2016T6R8M
L2: 18uH; L_0805_2012Metric
R3: 51k; R_0603_1608Metric_Pad0.98x0.95mm_HandSolder
R4, R6: 22.1k; R_0603_1608Metric_Pad0.98x0.95mm_HandSolder
R5: 88.7k; R_0603_1608Metric_Pad0.98x0.95mm_HandSolder
U4, U5: TPS5604; SOT-23-6

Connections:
+3.3V: C5.1, L1.2, R3.1; also elsewhere on the board
+5V: C3.1, C8.1, L2.2, R5.1, U4.4 (EN), U4.5 (VIN); also elsewhere on the board
+24V: C6.1, C44.1, C45.1, C46.1, C47.1, D6.1 (K), F1.2, U5.4 (EN), U5.5 (VIN); also elsewhere on the board
GND: C3.2, C5.2, C6.2, C8.2, C44.2, C45.2, C46.2, C47.2, D6.2 (A), H1.1 (1_1), H2.1 (1_1), H3.1 (1_1), H4.1 (1_1), J15.3, J15.4, R4.1, R6.1, U4.2 (GND), U5.2 (GND); also elsewhere on the board
unnamed: F1.1, J15.1, J15.2
unnamed: C4.1, U4.1 (CB)
unnamed: R3.2, R4.2, U4.3 (FB)
unnamed: C4.2, L1.1, U4.6 (SW)
unnamed: C7.1, U5.1 (CB)
unnamed: R5.2, R6.2, U5.3 (FB)
unnamed: C7.2, L2.1, U5.6 (SW)

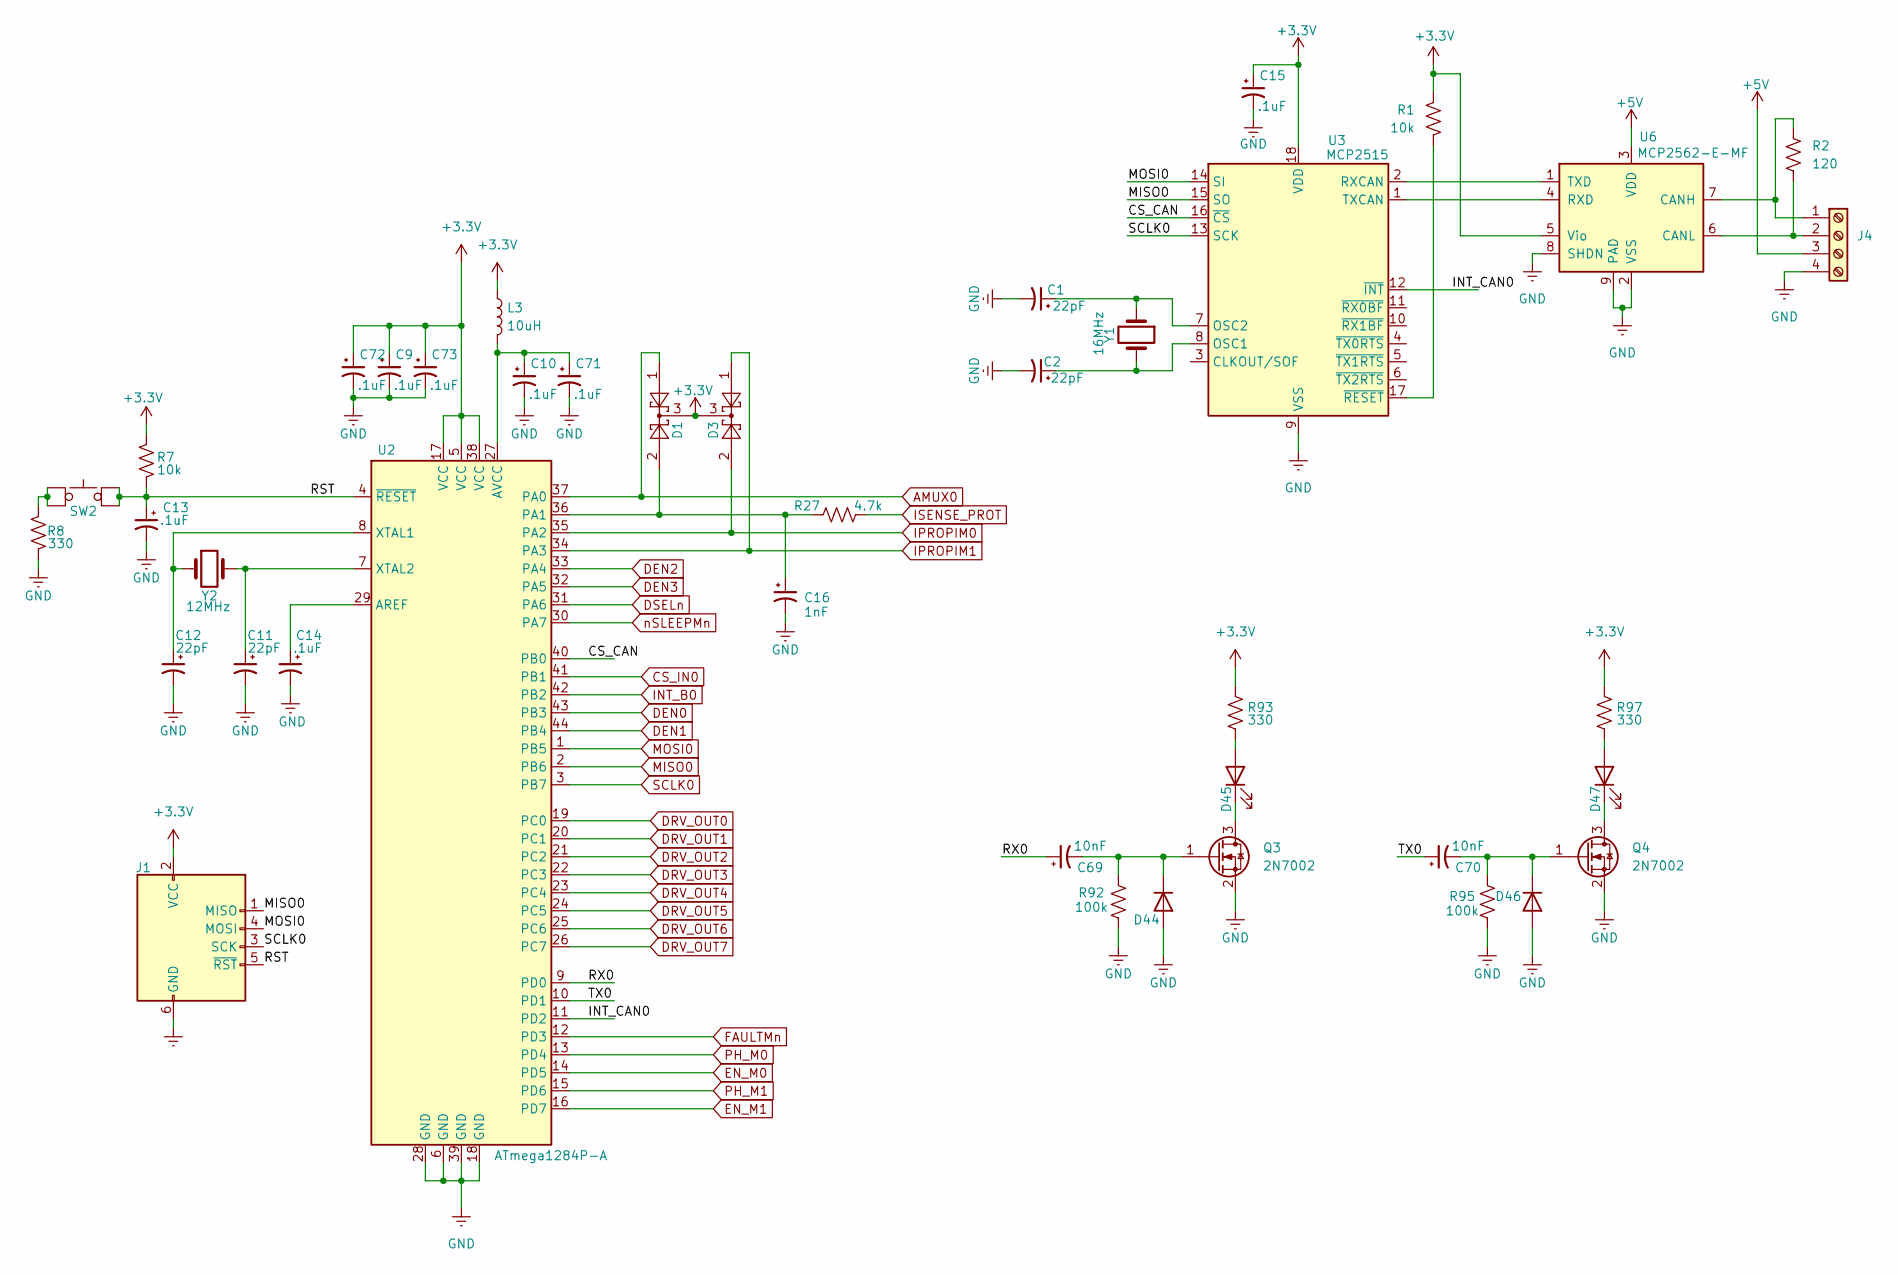
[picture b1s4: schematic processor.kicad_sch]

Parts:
C1, C2, C11, C12: 22pF; C_0603_1608Metric
C9, C10, C13, C14, C15, C71, C72, C73: .1uF; C_0603_1608Metric
C16: 1nF; C_0603_1608Metric
C69, C70: 10nF; C_0603_1608Metric
D1, D3: BAT54C; SOT-23
D44, D46: 1N4148W; D_SOD-123
D45, D47: LED; LED_0603_1608Metric
J1: AVR-ISP-6; PinHeader_2x03_P2.54mm_Vertical_SMD
J4: Screw_Terminal_01x04; PhoenixContact_MSTBA_2,5_4-G-5,08_1x04_P5.08mm_Horizontal
L3: 10uH; C_0603_1608Metric
Q3, Q4: 2N7002; SOT-23
R1, R7: 10k; R_0603_1608Metric_Pad0.98x0.95mm_HandSolder
R2: 120; R_0603_1608Metric_Pad0.98x0.95mm_HandSolder
R8, R93, R97: 330; R_0603_1608Metric_Pad0.98x0.95mm_HandSolder
R27: 4.7k; R_0603_1608Metric_Pad0.98x0.95mm_HandSolder
R92, R95: 100k; R_0603_1608Metric_Pad0.98x0.95mm_HandSolder
SW2: EVQ-P9W02W; KEY-SMD_EVQP9W02W
U2: ATmega1284P-A; TQFP-44_10x10mm_P0.8mm
U3: MCP2515; QFN-20-1EP_4x4mm_P0.5mm_EP2.5x2.5mm
U6: MCP2562-E-MF; SOIC-8-1EP_3.9x4.9mm_P1.27mm_EP2.29x3mm_ThermalVias
Y1: 16MHz; WE-XTAL_CFPX-180
Y2: 12MHz; WE-XTAL_CFPX-180

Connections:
+3.3V: C9.1, C15.1, C72.1, C73.1, D1.3, D3.3, J1.2 (VCC), L3.1, R1.1, R7.1, R93.2, R97.2, U2.5 (VCC), U2.17 (VCC), U2.38 (VCC), U3.18 (VDD), U6.5 (Vio); also elsewhere on the board
+5V: J4.3, U6.3 (VDD); also elsewhere on the board
/processor/CS_CAN: U2.40 (PB0), U3.16 (~CS)
/processor/INT_CAN0: U2.11 (PD2), U3.12 (~INT)
/processor/RX0: C69.1, U2.9 (PD0)
/processor/TX0: C70.1, U2.10 (PD1)
AMUX0: D1.1, U2.37 (PA0); also elsewhere on the board
CS_IN0: U2.41 (PB1); also elsewhere on the board
DEN0: U2.43 (PB3); also elsewhere on the board
DEN1: U2.44 (PB4); also elsewhere on the board
DEN2: U2.33 (PA4); also elsewhere on the board
DEN3: U2.32 (PA5); also elsewhere on the board
DRV_OUT0: U2.19 (PC0); also elsewhere on the board
DRV_OUT1: U2.20 (PC1); also elsewhere on the board
DRV_OUT2: U2.21 (PC2); also elsewhere on the board
DRV_OUT3: U2.22 (PC3); also elsewhere on the board
DRV_OUT4: U2.23 (PC4); also elsewhere on the board
DRV_OUT5: U2.24 (PC5); also elsewhere on the board
DRV_OUT6: U2.25 (PC6); also elsewhere on the board
DRV_OUT7: U2.26 (PC7); also elsewhere on the board
DSELn: U2.31 (PA6); also elsewhere on the board
EN_M0: U2.14 (PD5); also elsewhere on the board
EN_M1: U2.16 (PD7); also elsewhere on the board
FAULTMn: U2.12 (PD3); also elsewhere on the board
GND: C1.2, C2.2, C9.2, C10.2, C11.2, C12.2, C13.2, C14.2, C15.2, C16.2, C71.2, C72.2, C73.2, D44.2 (A), D46.2 (A), J1.6 (GND), J4.4, Q3.2 (S), Q4.2 (S), R8.1, R92.1, R95.1, U2.6 (GND), U2.18 (GND), U2.28 (GND), U2.39 (GND), U3.9 (VSS), U6.2 (VSS), U6.8 (SHDN), U6.9 (PAD); also elsewhere on the board
INT_B0: U2.42 (PB2); also elsewhere on the board
IPROPIM0: D3.2, U2.35 (PA2); also elsewhere on the board
IPROPIM1: D3.1, U2.34 (PA3); also elsewhere on the board
ISENSE_PROT: R27.2; also elsewhere on the board
MISO0: J1.1 (MISO), U2.2 (PB6), U3.15 (SO); also elsewhere on the board
MOSI0: J1.4 (MOSI), U2.1 (PB5), U3.14 (SI); also elsewhere on the board
unnamed: C69.2, D44.1 (K), Q3.1 (G), R92.2
unnamed: D45.2 (A), R93.1
unnamed: D45.1 (K), Q3.3 (D)
unnamed: C70.2, D46.1 (K), Q4.1 (G), R95.2
unnamed: D47.2 (A), R97.1
unnamed: D47.1 (K), Q4.3 (D)
unnamed: J4.1, R2.1, U6.7 (CANH)
unnamed: J4.2, R2.2, U6.6 (CANL)
unnamed: C14.1, U2.29 (AREF)
unnamed: C10.1, C71.1, L3.2, U2.27 (AVCC)
unnamed: C16.1, D1.2, R27.1, U2.36 (PA1)
unnamed: C12.1, U2.8 (XTAL1), Y2.1
unnamed: C11.1, U2.7 (XTAL2), Y2.3
unnamed: C2.1, U3.8 (OSC1), Y1.3
unnamed: C1.1, U3.7 (OSC2), Y1.1
unnamed: U3.2 (RXCAN), U6.1 (TXD)
unnamed: U3.1 (TXCAN), U6.4 (RXD)
unnamed: R1.2, U3.17 (~RESET)
PH_M0: U2.13 (PD4); also elsewhere on the board
PH_M1: U2.15 (PD6); also elsewhere on the board
SCLK0: J1.3 (SCK), U2.3 (PB7), U3.13 (SCK); also elsewhere on the board
nSLEEPMn: U2.30 (PA7); also elsewhere on the board

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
